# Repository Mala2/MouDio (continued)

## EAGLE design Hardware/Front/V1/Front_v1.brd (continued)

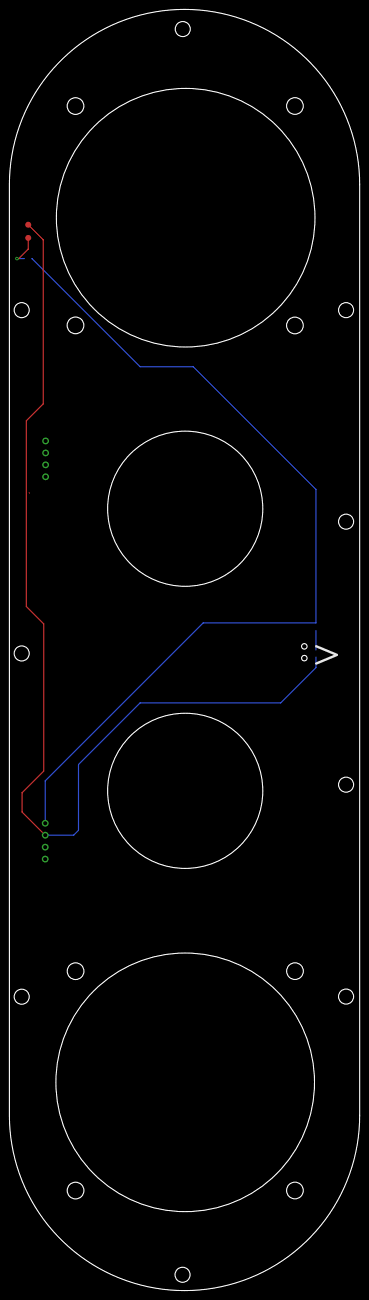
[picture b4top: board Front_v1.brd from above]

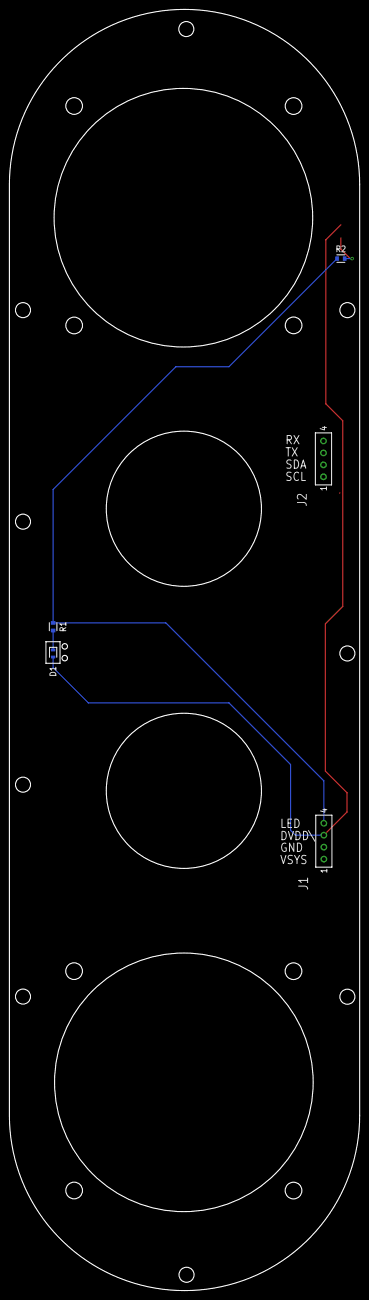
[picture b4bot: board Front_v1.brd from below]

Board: 2 copper layers, 74.5 x 272.5 mm, 8 parts (6 on the bottom side), 4 nets.

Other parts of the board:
U$1: SLP3-150-300-F; SLP3-150-300-F1

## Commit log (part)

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2021-10-06 Create Laser Cut
2021-10-08 Create LICENSE
2021-10-08 Set theme jekyll-theme-cayman
2022-01-09 NEWEST REQUIREMENTS
2022-01-12 added
2022-01-12 Revert "added"
    This reverts commit fa20d2665205bb29a5a4202c796f6a7fb5f905b6.
2022-01-12 Revert "Merge branch 'main' of https://github.com/Mala2/Bluetooth-Speaker"
    This reverts commit 116b261c082d1031f2e74fd34bcdcf441b9425dc, reversing
    changes made to 56635f97e87aed3de2d24668a59d18ce55737f49.
2022-01-12 Code
2022-01-13 ADDED BLOCK DIAGRAM
2022-01-14 add gif
2022-01-31 UPDATE SW
2022-02-09 Update HW Files
2022-02-11 TEST
2022-02-11 Revert "Merge branch 'main' of https://github.com/Mala2/Bluetooth-Speaker"
    This reverts commit 87ac8f8a3c6f25865529e84b1821ee6b6bf29b79, reversing
    changes made to ee49ae8c5d0874985522064465cb78c6d77b9581.
2022-02-11 FRONT
2022-02-22 BLOCK DIAGRAM UP
2022-02-22 Revert "Add files via upload"
    This reverts commit fd3c556a91f004d5246b1b8f4f1818f6bf354c4a.
2022-02-22 Revert "Merge branch 'main' of https://github.com/Mala2/Bluetooth-Speaker"
    This reverts commit e171d9436b2d321118c9aa79e2768390a09b15c9, reversing
    changes made to 264b2a50b00b703b2ac44931e94717ab832d0f34.
2022-02-22 Revert "Update .DS_Store"
    This reverts commit 1e42d3a8f7f45ec3107d97a5940b6a850ea9f1c4.
2022-02-22 Revert "1"
    This reverts commit 349bce1e51d128c908e9f4acd0fad1693c182c78.
2022-02-24 Main
2022-02-24 Revert "Delete Main Front V1.png"
    This reverts commit c3250bed3c48fc1f3d306a4ad13a38debea811c1.
2022-02-24 Revert "Merge branch 'main' of https://github.com/Mala2/Bluetooth-Speaker"
    This reverts commit a6c1021ec30da70af2b6a883bb426584a599d5b4, reversing
    changes made to 0adeb03ef37f2a7b293e844453b9da7cafdc62e4.
2022-02-24 Revert "Merge branch 'main' of https://github.com/Mala2/Bluetooth-Speaker"
    This reverts commit 0adeb03ef37f2a7b293e844453b9da7cafdc62e4, reversing
    changes made to cfb3c7db4c7f6475e6a54a10a37ae036b7728dbd.
2022-02-24 Revert "Update Main Front V1.png"
    This reverts commit cfb3c7db4c7f6475e6a54a10a37ae036b7728dbd.
2022-02-24 Revert "Create Main Front V1.png"
    This reverts commit 16df5e12202520973b071a89de1ca294a4b583bf.
2022-02-24 Revert "Delete Main Front V1.png"
    This reverts commit 430e595c493235a1283df6d0e6aa2082400ccd1d.
2022-02-28 Added front
2022-03-03 Add the 3d file
2022-03-03 Revert "Add the 3d file"
    This reverts commit 08c1c1ded88cbf59e5bfefa92130c16ca75dee5a.
2022-03-23 Software
2022-12-02 Updates 3d files
2022-12-02 Updates pics
2022-12-02 updates 1
